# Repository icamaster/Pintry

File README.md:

## Introduction
The Pintry X2 is a two bay NAS (Network Attached Storage) based on the Raspberry Pi Compute Module 4. It uses the ASMedia AS1061 PCIe to Sata bridge to connect up to 2 drives (3.5'/2.5' HDD or 2.5' SSD) to the SoM running a Linux based OS (Raspberry Pi OS).

## Website
Here is a link for additional information: https://www.cezarchirila.com/projects/pintry-x2.html

## Features
* Supports both CM4 and CM4 lite variants
* 2 x SATA ports with power using ASM1061. It should work with both 2.5' and 3.5' HDDs/SSDs but so far it has only been tested with 2.5' SSDs (Western Digital WDS500G2B0A)
* On/Off switch - Can both wake up the CM4 or shut it down (see Device Tree Overlay section) 
* 2 x Fan headers (PWM pin connected, Tach pin unconnected)
* 12V Input Power (max 5A, required for 3.5' drives). 
* USB 2.0 Host port for connecting USB devices and a microUSB Device port for updating the eMMC on CM4. 
* Expander header for access to various GPIO

## Names have a meaning
Pi + Pantry = Pintry

## Device Tree Overlay
Add these changes at the end of the /boot/config.txt to enable specific functionality:
```
# Enable FAN control for FAN0
dtoverlay=gpio-fan,gpiopin=12

# Enable FAN control for FAN1
#dtoverlay=gpio-fan,gpiopin=13

# Enable full functionality of On/Off button
dtoverlay=gpio-shutdown,gpio_pin=21,active_low=0,gpio_pull=off

# Enable UART - UNTESTED
#dtoverlay=uart0,txd0_pin=14,rxd0_pin=15,pin_func=4
#enable_uart=1  
```
Remember to remove the '#' in from of options you want to enable. 

## Kernel
Previously, to be able to use SATA drives with a CM4 you had to recompile the kernel with added SATA support. See instructions [here](https://github.com/geerlingguy/raspberry-pi-pcie-devices/issues/1#issuecomment-717578358) (credit to [Jeff Geerling](github.com/geerlingguy) for instructions). However, newer kernel versions have SATA support built-in, so you should not have to worry about this.

## Enclosure
The enclosure supports 2.5' drives only. It does not have any mounting features for fans, but there is room for a 60mm fan on the bottom as shown in the images below. It does not need supports for printing. Designed in Fusion 360.

For assembly, you will need the following:
* 4 x M3 brass inserts (D0.46mm, L0.57mm)
* 4 x M3x18mm socket screws - for mounting the drives 
* 4 x M3x25mm socket screws - for mounting the drives
* 4 x M3x35mm socket screws - for joining the two halves of the enclosure

## Thermal management
To keep temperatures under control, I have used a RAM heatsink on the ASM1061 IC and a 60mm fan on the bottom of the enclosure tied to the FAN header and controlled via the 'gpio-fan' overlay. It is mounted in such way that it blows air over both the CM4 and the ASM1061.  

## Release
The current latest release is V1.1. This version has not been tested or manufactured yet, therefore I would suggest double checking it if you plan on bulding it!
All the necessary manufacturing and assembly files are in the 'OutputJob/Version' and 'Enclosure' folders.

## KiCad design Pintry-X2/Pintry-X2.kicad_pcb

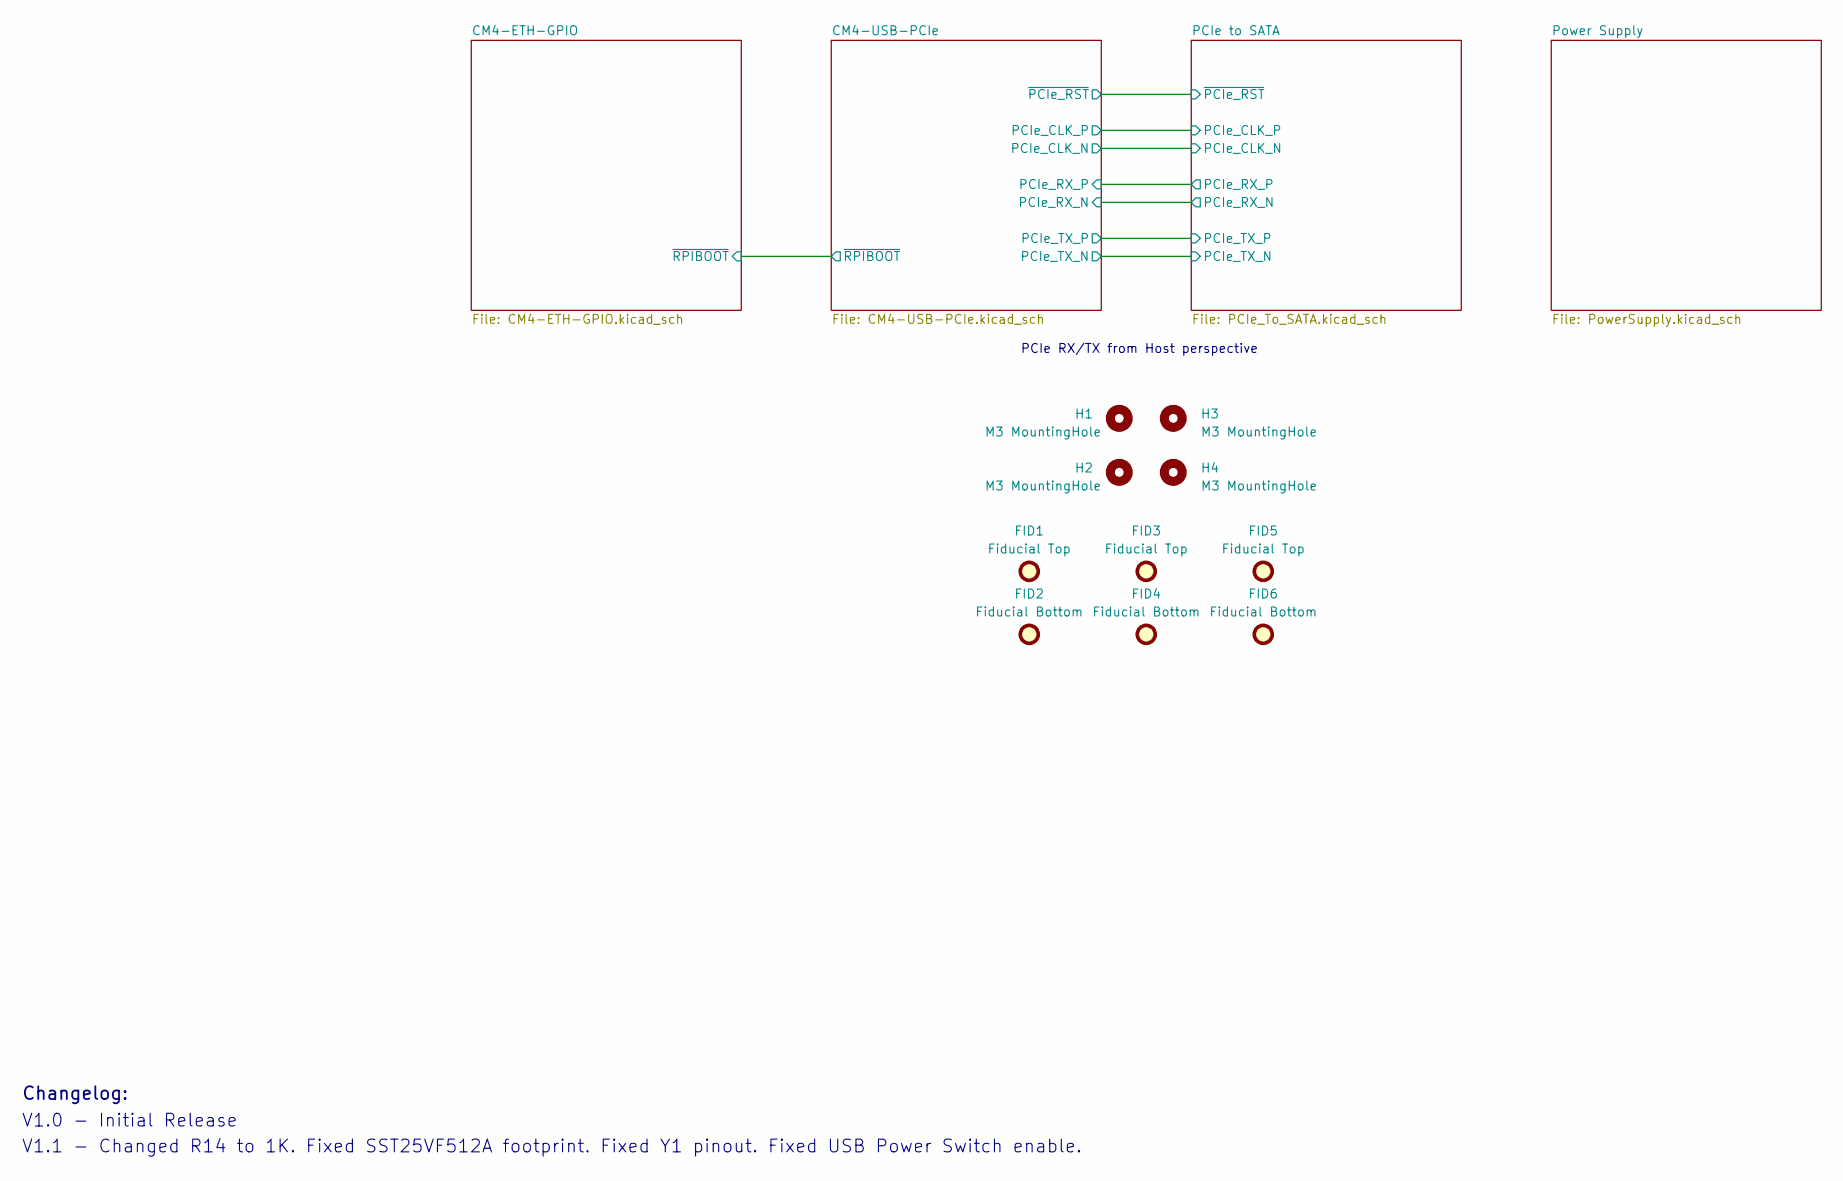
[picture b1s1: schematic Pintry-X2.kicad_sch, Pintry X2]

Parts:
FID1, FID3, FID5: Fiducial Top; Fiducial_1mm_Mask2mm
FID2, FID4, FID6: Fiducial Bottom; Fiducial_1mm_Mask2mm
H1, H2, H3, H4: M3 MountingHole; MountingHole_3.2mm_M3

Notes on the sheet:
V1.0 - Initial Release
Changelog:
PCIe RX/TX from Host perspective
V1.1 - Changed R14 to 1K. Fixed SST25VF512A footprint. Fixed Y1 pinout. Fixed USB Power Switch enable.

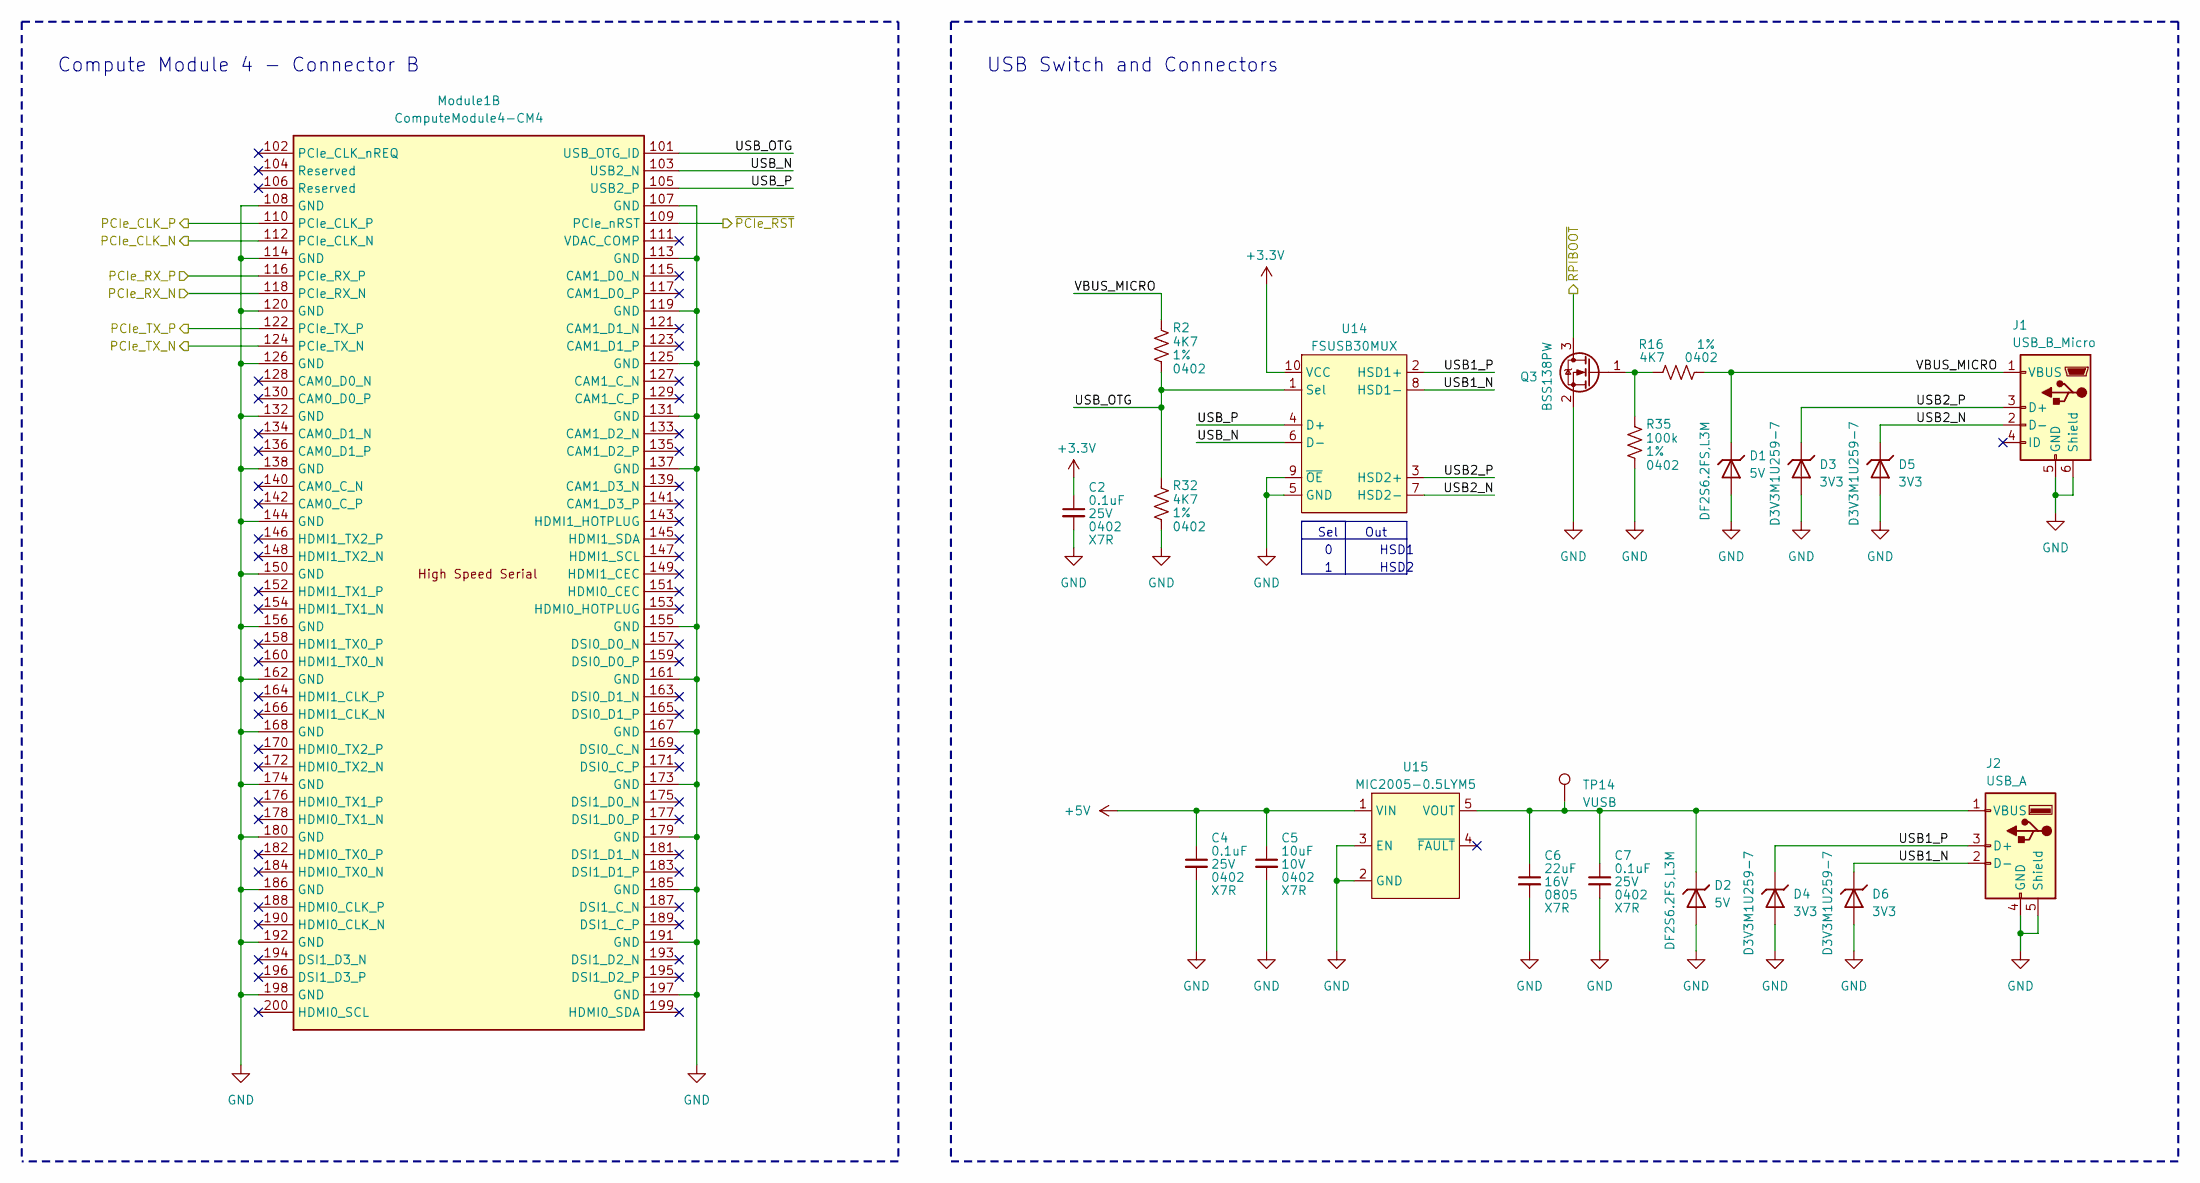
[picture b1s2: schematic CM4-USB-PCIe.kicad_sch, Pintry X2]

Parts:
C2, C4, C7: 0.1uF; C_0402_1005Metric; Voltage Rating 25V
C5: 10uF; C_0402_1005Metric; Voltage Rating 10V
C6: 22uF; C_0805_2012Metric; Voltage Rating 16V; Part Number GRM21BR61A226ME51L
D1, D2: DF2S6.2FS,L3M; D_SOD-923; Part Number DF2S6.2FS,L3M
D3, D4, D5, D6: D3V3M1U259-7; D_SOD-923; Part Number D3V3M1U2S9-7
J1: USB_B_Micro; USB_Micro-B_Amphenol_10103594-0001LF_Horizontal; Part Number 10103594-0001LF
J2: USB_A; USB_A_Amphenol_ICC_73725-11A0BLF_Horizontal; Part Number 73725-11A0BLF
Module1: ComputeModule4-CM4; Raspberry-Pi-4-Compute-Module; Part Number 2x DF40C-100DS-0.4V
Q3: BSS138PW; SOT-323_SC-70; Part Number BSS138PW,115
R2, R16, R32: 4K7; R_0402_1005Metric; Tolerance 1%
R35: 100k; R_0402_1005Metric; Tolerance 1%
TP14: VUSB; TestPoint_Pad_D1.0mm
U14: FSUSB30MUX; MSOP-10_3x3mm_P0.5mm; Part Number FSUSB30MUX
U15: MIC2005-0.5LYM5; SOT-23-5; Part Number MIC2005-0.5LYM5

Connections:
+3V3: C2.1, U14.10 (VCC); also elsewhere on the board
+5V: C4.1, C5.1, U15.1 (VIN); also elsewhere on the board
/CM4-ETH-GPIO/~RPIBOOT: Q3.3 (D); also elsewhere on the board
/CM4-USB-PCIe/PCIe_CLK_N: Module1.112 (PCIe_CLK_N); also elsewhere on the board
/CM4-USB-PCIe/PCIe_CLK_P: Module1.110 (PCIe_CLK_P); also elsewhere on the board
/CM4-USB-PCIe/PCIe_RX_N: Module1.118 (PCIe_RX_N); also elsewhere on the board
/CM4-USB-PCIe/PCIe_RX_P: Module1.116 (PCIe_RX_P); also elsewhere on the board
/CM4-USB-PCIe/PCIe_TX_N: Module1.124 (PCIe_TX_N); also elsewhere on the board
/CM4-USB-PCIe/PCIe_TX_P: Module1.122 (PCIe_TX_P); also elsewhere on the board
/CM4-USB-PCIe/USB1_N: D6.1 (K), J2.2 (D-), U14.8 (HSD1-)
/CM4-USB-PCIe/USB1_P: D4.1 (K), J2.3 (D+), U14.2 (HSD1+)
/CM4-USB-PCIe/USB2_N: D5.1 (K), J1.2 (D-), U14.7 (HSD2-)
/CM4-USB-PCIe/USB2_P: D3.1 (K), J1.3 (D+), U14.3 (HSD2+)
/CM4-USB-PCIe/USB_N: Module1.103 (USB2_N), U14.6 (D-)
/CM4-USB-PCIe/USB_OTG: Module1.101 (USB_OTG_ID), R2.2, R32.1, U14.1 (Sel)
/CM4-USB-PCIe/USB_P: Module1.105 (USB2_P), U14.4 (D+)
/CM4-USB-PCIe/VBUS_MICRO: D1.1 (K), J1.1 (VBUS), R2.1, R16.2
/CM4-USB-PCIe/~PCIe_RST: Module1.109 (PCIe_nRST); also elsewhere on the board
GND: C2.2, C4.2, C5.2, C6.2, C7.2, D1.2 (A), D2.2 (A), D3.2 (A), D4.2 (A), D5.2 (A), D6.2 (A), J1.5 (GND), J1.6 (Shield), J2.4 (GND), J2.5 (Shield), Module1.107 (GND), Module1.108 (GND), Module1.113 (GND), Module1.114 (GND), Module1.119 (GND), Module1.120 (GND), Module1.125 (GND), Module1.126 (GND), Module1.131 (GND), Module1.132 (GND), Module1.137 (GND), Module1.138 (GND), Module1.144 (GND), Module1.150 (GND), Module1.155 (GND), Module1.156 (GND), Module1.161 (GND), Module1.162 (GND), Module1.167 (GND), Module1.168 (GND), Module1.173 (GND), Module1.174 (GND), Module1.179 (GND), Module1.180 (GND), Module1.185 (GND), Module1.186 (GND), Module1.191 (GND), Module1.192 (GND), Module1.197 (GND), Module1.198 (GND), Q3.2 (S), R32.2, R35.2, U14.5 (GND), U14.9 (~OE), U15.2 (GND), U15.3 (EN); also elsewhere on the board
unnamed: C6.1, C7.1, D2.1 (K), J2.1 (VBUS), TP14.1, U15.5 (VOUT)
unnamed: Q3.1 (G), R16.1, R35.1

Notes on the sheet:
Compute Module 4 - Connector B
Sel Out
USB Switch and Connectors
1 HSD2
0 HSD1

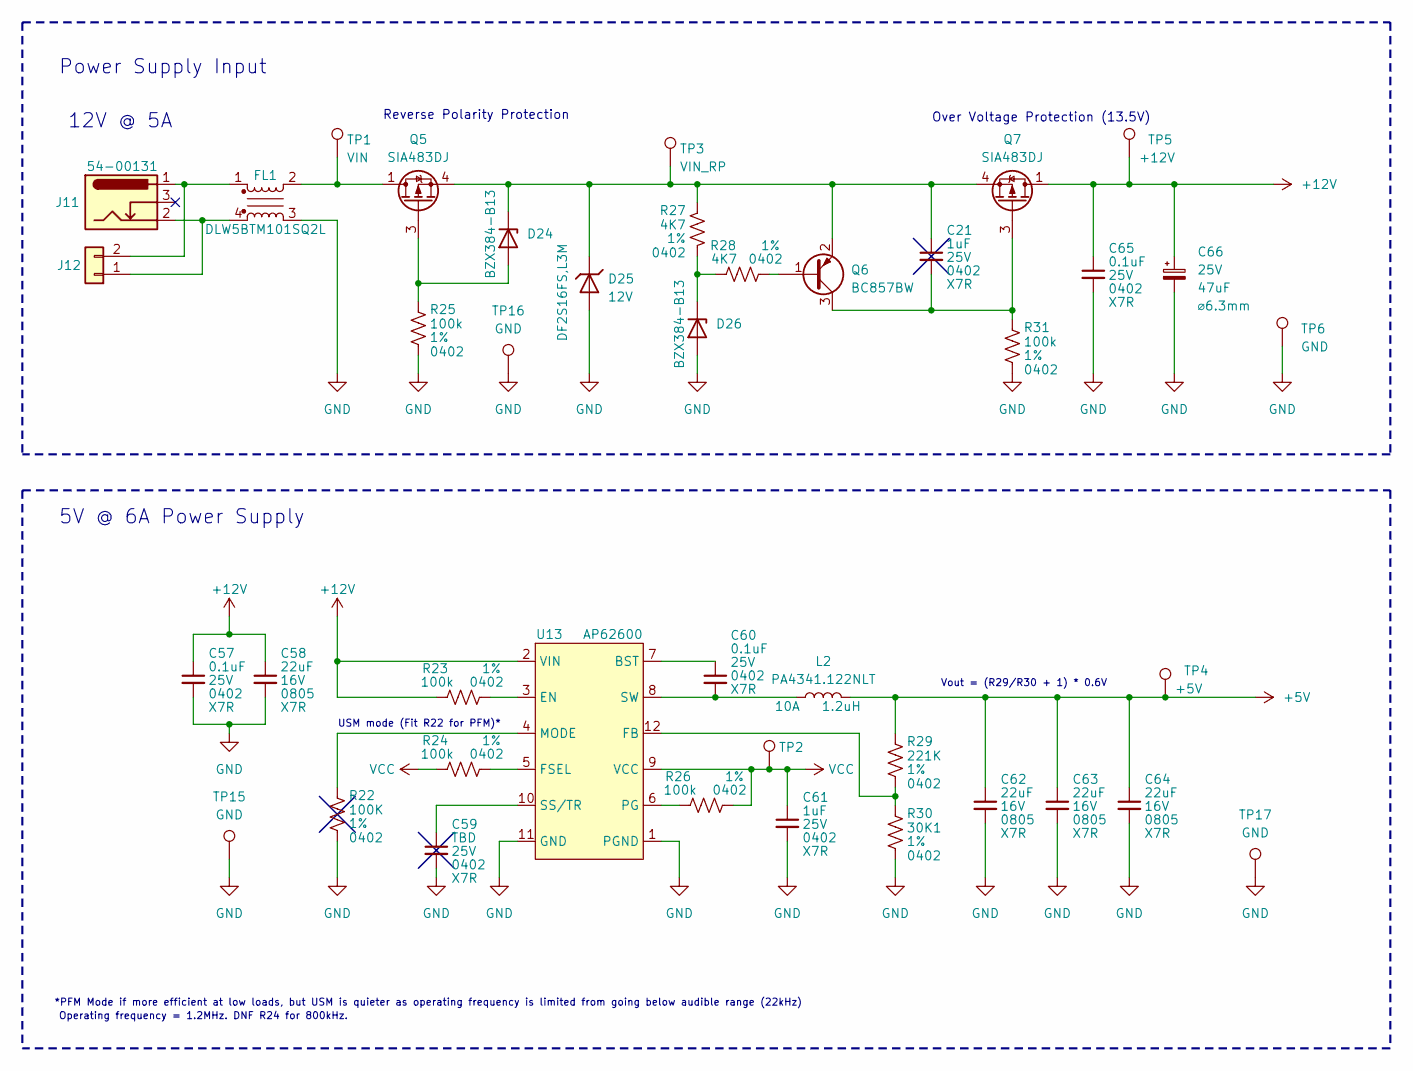
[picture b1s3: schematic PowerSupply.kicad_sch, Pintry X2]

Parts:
C21, C61: 1uF; C_0402_1005Metric; Voltage Rating 25V
C57, C60, C65: 0.1uF; C_0402_1005Metric; Voltage Rating 25V
C58: 22uF; C_0805_2012Metric; Voltage Rating 16V; Part Number CL21A226MOQNNNE
C59: TBD; C_0402_1005Metric; Voltage Rating 25V
C62, C63, C64: 22uF; C_0805_2012Metric; Voltage Rating 16V; Part Number GRM21BR61A226ME51L
C66: 865080443007; CP_Elec_6.3x5.4; Voltage 25V; Part Number 865080443007
D24, D26: BZX384-B13; D_SOD-323; Part Number BZX384-B13,115
D25: DF2S16FS,L3M; D_SOD-923; Part Number DF2S16FS,L3M
FL1: DLW5BTM101SQ2L; Part Number DLW5BTM101SQ2L
J11: 54-00131; Part Number 54-00131
J12: Alternate Power Connector; SolderWire-1sqmm_1x02_P5.4mm_D1.4mm_OD2.7mm
L2: PA4341.122NLT; Pulse_PA4341; Current Rating 10A; Part Number PA4341.122NLT
Q5, Q7: SIA483DJ; Vishay_PowerPAK_SC70-6L_Single; PartNumber SIA483DJ-T1-GE3
Q6: BC857BW; SOT-323_SC-70; Part Number BC857BW,135
R22: 100K; R_0402_1005Metric; Tolerance 1%
R23, R24, R25, R26, R31: 100k; R_0402_1005Metric; Tolerance 1%
R27, R28: 4K7; R_0402_1005Metric; Tolerance 1%
R29: 221K; R_0402_1005Metric; Tolerance 1%
R30: 30K1; R_0402_1005Metric; Tolerance 1%
TP1: VIN; TestPoint_Pad_D1.0mm
TP2: VCC; TestPoint_Pad_D1.0mm
TP3: VIN_RP; TestPoint_Pad_D1.0mm
TP4: +5V; TestPoint_Pad_D1.0mm
TP5: +12V; TestPoint_Pad_D1.0mm
TP6, TP15, TP16, TP17: GND; TestPoint_Pad_D1.0mm
U13: AP62600; V-QFN2030-12 (Type A); Part Number AP62600SJ-7

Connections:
+5V: C62.1, C63.1, C64.1, L2.2, R29.1, TP4.1; also elsewhere on the board
+12V: C57.1, C58.1, C65.1, C66.1, Q7.1 (D), R23.1, TP5.1, U13.2 (VIN); also elsewhere on the board
GND: C57.2, C58.2, C59.2, C61.2, C62.2, C63.2, C64.2, C65.2, C66.2, D25.2 (A), D26.2 (A), FL1.3, R22.2, R25.2, R30.2, R31.2, TP6.1, TP15.1, TP16.1, TP17.1, U13.1 (PGND), U13.11 (GND); also elsewhere on the board
unnamed: C21.1, D24.1 (K), D25.1 (K), Q5.4 (S), Q6.2 (E), Q7.4 (S), R27.1, TP3.1
unnamed: C21.2, Q6.3 (C), Q7.3 (G), R31.1
unnamed: C59.1, U13.10 (SS/TR)
unnamed: C60.1, U13.7 (BST)
unnamed: C60.2, L2.1, U13.8 (SW)
unnamed: D24.2 (A), Q5.3 (G), R25.1
unnamed: D26.1 (K), R27.2, R28.1
unnamed: FL1.1, J11.1 (A), J12.2
unnamed: FL1.2, Q5.1 (D), TP1.1
unnamed: FL1.4, J11.2 (B), J12.1
unnamed: Q6.1 (B), R28.2
unnamed: R22.1, U13.4 (MODE)
unnamed: R23.2, U13.3 (EN)
unnamed: R24.2, U13.5 (FSEL)
unnamed: R26.1, U13.6 (PG)
unnamed: R29.2, R30.1, U13.12 (FB)
VCC: C61.1, R24.1, R26.2, TP2.1, U13.9 (VCC)

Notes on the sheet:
5V @ 6A Power Supply
Power Supply Input
12V @ 5A
USM mode (Fit R22 for PFM)*
Vout = (R29/R30 + 1) * 0.6V
Operating frequency = 1.2MHz. DNF R24 for 800kHz.
*PFM Mode if more efficient at low loads, but USM is quieter as operating frequency is limited from going below audible range (22kHz)
Reverse Polarity Protection
Over Voltage Protection (13.5V)

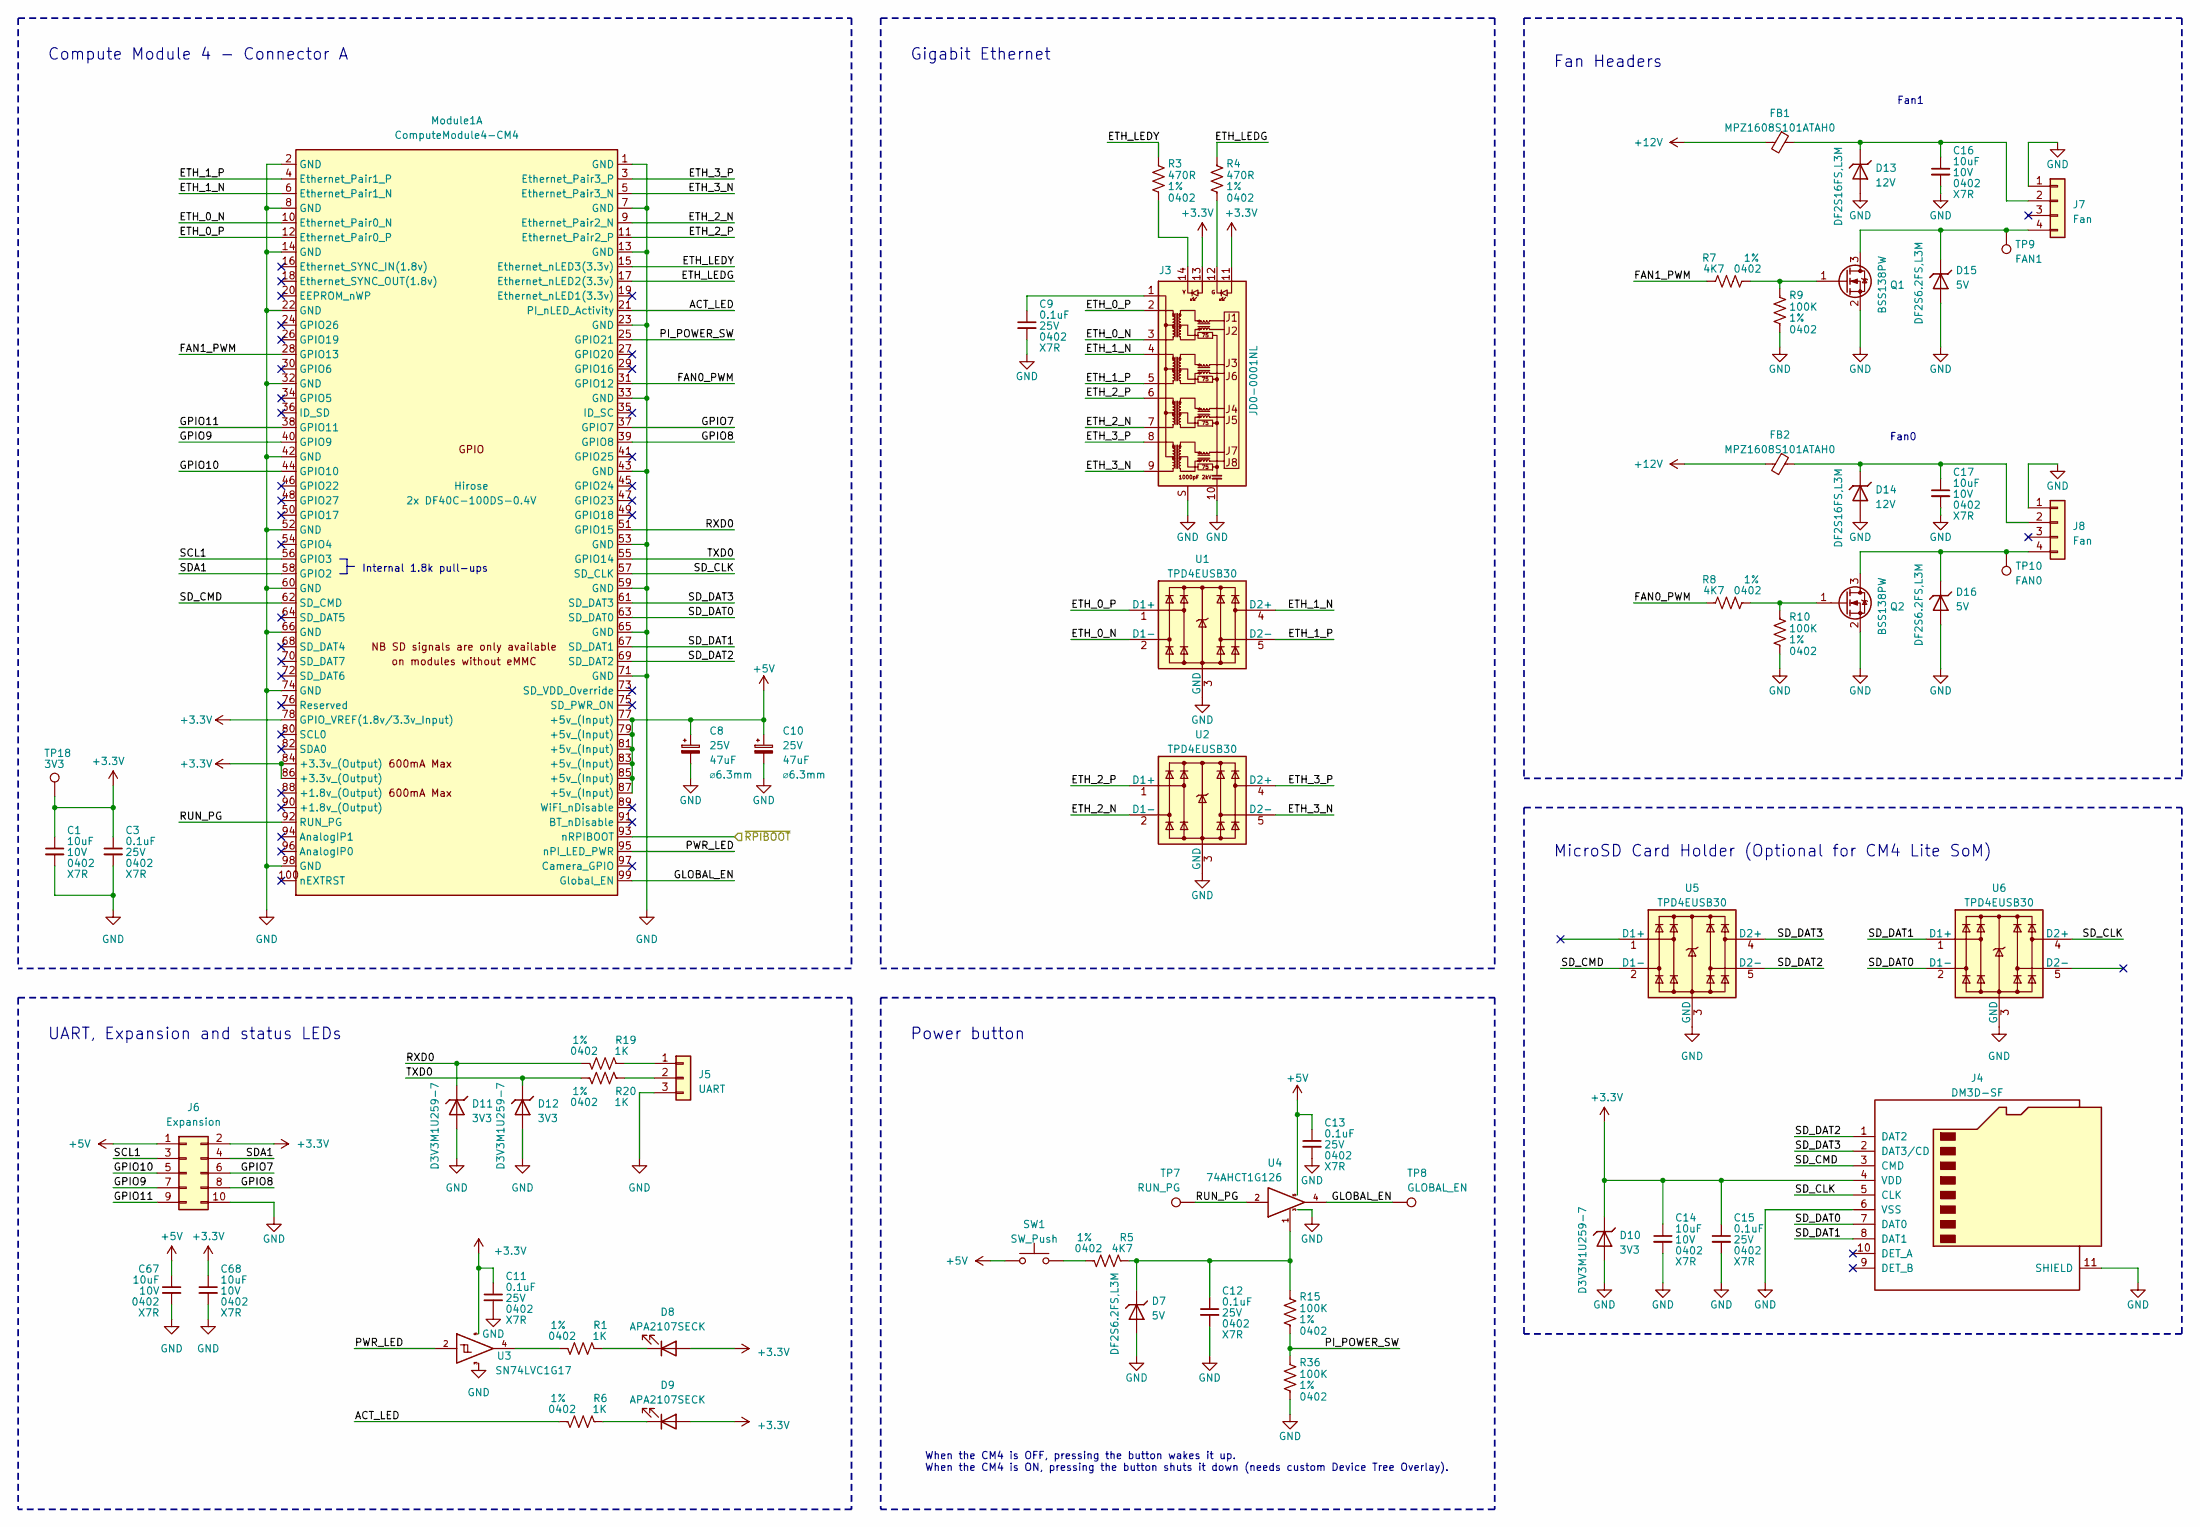
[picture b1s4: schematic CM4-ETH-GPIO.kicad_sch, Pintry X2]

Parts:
C1, C14, C16, C17, C67, C68: 10uF; C_0402_1005Metric; Voltage Rating 10V
C3, C9, C11, C12, C13, C15: 0.1uF; C_0402_1005Metric; Voltage Rating 25V
C8, C10: 865080443007; CP_Elec_6.3x5.4; Voltage 25V; Part Number 865080443007
D7, D15, D16: DF2S6.2FS,L3M; D_SOD-923; Part Number DF2S6.2FS,L3M
D8, D9: APA2107SECK; PartNumber APA2107SECK/J4-PRV
D10, D11, D12: D3V3M1U259-7; D_SOD-923; Part Number D3V3M1U2S9-7
D13, D14: DF2S16FS,L3M; D_SOD-923; Part Number DF2S16FS,L3M
FB1, FB2: MPZ1608S101ATAH0; L_0603_1608Metric; Part Number MPZ1608S101ATAH0
J3: JD0-0001NL; Pulse-JD0-0001NL-0-0-MFG; Part Number JD0-0001NL
J4: DM3D-SF; microSD_HC_Hirose_DM3D-SF; Part Number DM3D-SF
J5: UART; PinHeader_1x03_P2.54mm_Vertical; Part Number PH1-03-UA
J6: Expansion; PinHeader_2x05_P2.54mm_Vertical; Part Number 2PH2-10-UA
J7, J8: Fan; Molex_KK-254_AE-6410-04A_1x04_P2.54mm_Vertical; Part Number 47053-1000
Module1: ComputeModule4-CM4; Raspberry-Pi-4-Compute-Module; Part Number 2x DF40C-100DS-0.4V
Q1, Q2: BSS138PW; SOT-323_SC-70; Part Number BSS138PW,115
R1, R6, R19, R20: 1K; R_0402_1005Metric; Tolerance 1%
R3, R4: 470R; R_0402_1005Metric; Tolerance 1%
R5, R7, R8: 4K7; R_0402_1005Metric; Tolerance 1%
R9, R10, R15, R36: 100K; R_0402_1005Metric; Tolerance 1%
SW1: SW_Push; SW_Tactile_SPST_Angled_PTS645Vx58-2LFS; Part Number 1-1825027-4
TP7: RUN_PG; TestPoint_Pad_D1.0mm
TP8: GLOBAL_EN; TestPoint_Pad_D1.0mm
TP9: FAN1; TestPoint_Pad_D1.0mm
TP10: FAN0; TestPoint_Pad_D1.0mm
TP18: 3V3; TestPoint_Pad_D1.0mm
U1, U2, U5, U6: TPD4EUSB30; USON-10_2.5x1.0mm_P0.5mm; Part Number TPD4EUSB30DQAR
U3: SN74LVC1G17; SOT-23-5; Part Number SN74LVC1G17DBVR
U4: 74AHCT1G126; SOT-353_SC-70-5; Part Number 74AHCT1G126SE-7

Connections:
+3V3: C1.1, C3.1, C11.1, C14.1, C15.1, C68.1, D8.2 (A), D9.2 (A), D10.1 (K), J3.11, J3.13, J4.4 (VDD), J6.2, Module1.78 (GPIO_VREF(1.8v/3.3v_Input)), Module1.84 (+3.3v_(Output)), Module1.86 (+3.3v_(Output)), TP18.1, U3.5 (VCC); also elsewhere on the board
+5V: C8.1, C10.1, C13.1, C67.1, J6.1, Module1.77 (+5v_(Input)), Module1.79 (+5v_(Input)), Module1.81 (+5v_(Input)), Module1.83 (+5v_(Input)), Module1.85 (+5v_(Input)), Module1.87 (+5v_(Input)), SW1.1, U4.5 (VCC); also elsewhere on the board
+12V: FB1.2, FB2.2; also elsewhere on the board
/CM4-ETH-GPIO/ACT_LED: Module1.21 (PI_nLED_Activity), R6.2
/CM4-ETH-GPIO/ETH_0_N: J3.3, Module1.10 (Ethernet_Pair0_N), U1.2 (D1-), U1.9
/CM4-ETH-GPIO/ETH_0_P: J3.2, Module1.12 (Ethernet_Pair0_P), U1.1 (D1+), U1.10
/CM4-ETH-GPIO/ETH_1_N: J3.4, Module1.6 (Ethernet_Pair1_N), U1.4 (D2+), U1.7
/CM4-ETH-GPIO/ETH_1_P: J3.5, Module1.4 (Ethernet_Pair1_P), U1.5 (D2-), U1.6
/CM4-ETH-GPIO/ETH_2_N: J3.7, Module1.9 (Ethernet_Pair2_N), U2.2 (D1-), U2.9
/CM4-ETH-GPIO/ETH_2_P: J3.6, Module1.11 (Ethernet_Pair2_P), U2.1 (D1+), U2.10
/CM4-ETH-GPIO/ETH_3_N: J3.9, Module1.5 (Ethernet_Pair3_N), U2.5 (D2-), U2.6
/CM4-ETH-GPIO/ETH_3_P: J3.8, Module1.3 (Ethernet_Pair3_P), U2.4 (D2+), U2.7
/CM4-ETH-GPIO/ETH_LEDG: Module1.17 (Ethernet_nLED2(3.3v)), R4.1
/CM4-ETH-GPIO/ETH_LEDY: Module1.15 (Ethernet_nLED3(3.3v)), R3.1
/CM4-ETH-GPIO/FAN0_PWM: Module1.31 (GPIO12), R8.1
/CM4-ETH-GPIO/FAN1_PWM: Module1.28 (GPIO13), R7.1
/CM4-ETH-GPIO/GLOBAL_EN: Module1.99 (Global_EN), TP8.1, U4.4
/CM4-ETH-GPIO/GPIO7: J6.6, Module1.37 (GPIO7)
/CM4-ETH-GPIO/GPIO8: J6.8, Module1.39 (GPIO8)
/CM4-ETH-GPIO/GPIO9: J6.7, Module1.40 (GPIO9)
/CM4-ETH-GPIO/GPIO10: J6.5, Module1.44 (GPIO10)
/CM4-ETH-GPIO/GPIO11: J6.9, Module1.38 (GPIO11)
/CM4-ETH-GPIO/PI_POWER_SW: Module1.25 (GPIO21), R15.2, R36.1
/CM4-ETH-GPIO/PWR_LED: Module1.95 (nPI_LED_PWR), U3.2
/CM4-ETH-GPIO/RUN_PG: Module1.92 (RUN_PG), TP7.1, U4.2
/CM4-ETH-GPIO/RXD0: D11.1 (K), Module1.51 (GPIO15), R19.2
/CM4-ETH-GPIO/SCL1: J6.3, Module1.56 (GPIO3)
/CM4-ETH-GPIO/SDA1: J6.4, Module1.58 (GPIO2)
/CM4-ETH-GPIO/SD_CLK: J4.5 (CLK), Module1.57 (SD_CLK), U6.4 (D2+), U6.7
/CM4-ETH-GPIO/SD_CMD: J4.3 (CMD), Module1.62 (SD_CMD), U5.2 (D1-), U5.9
/CM4-ETH-GPIO/SD_DAT0: J4.7 (DAT0), Module1.63 (SD_DAT0), U6.2 (D1-), U6.9
/CM4-ETH-GPIO/SD_DAT1: J4.8 (DAT1), Module1.67 (SD_DAT1), U6.1 (D1+), U6.10
/CM4-ETH-GPIO/SD_DAT2: J4.1 (DAT2), Module1.69 (SD_DAT2), U5.5 (D2-), U5.6
/CM4-ETH-GPIO/SD_DAT3: J4.2 (DAT3/CD), Module1.61 (SD_DAT3), U5.4 (D2+), U5.7
/CM4-ETH-GPIO/TXD0: D12.1 (K), Module1.55 (GPIO14), R20.2
/CM4-ETH-GPIO/~RPIBOOT: Module1.93 (nRPIBOOT); also elsewhere on the board
GND: C1.2, C3.2, C8.2, C9.2, C10.2, C11.2, C12.2, C13.2, C14.2, C15.2, C16.2, C17.2, C67.2, C68.2, D7.2 (A), D10.2 (A), D11.2 (A), D12.2 (A), D13.2 (A), D14.2 (A), D15.2 (A), D16.2 (A), J3.10, J3.S, J4.6 (VSS), J4.11 (SHIELD), J5.3, J6.10, J7.1, J8.1, Module1.1 (GND), Module1.2 (GND), Module1.7 (GND), Module1.8 (GND), Module1.13 (GND), Module1.14 (GND), Module1.22 (GND), Module1.23 (GND), Module1.32 (GND), Module1.33 (GND), Module1.42 (GND), Module1.43 (GND), Module1.52 (GND), Module1.53 (GND), Module1.59 (GND), Module1.60 (GND), Module1.65 (GND), Module1.66 (GND), Module1.71 (GND), Module1.74 (GND), Module1.98 (GND), Q1.2 (S), Q2.2 (S), R9.2, R10.2, R36.2, U1.3 (GND), U1.8 (GND), U2.3 (GND), U2.8 (GND), U3.3 (GND), U4.3 (GND), U5.3 (GND), U5.8 (GND), U6.3 (GND), U6.8 (GND); also elsewhere on the board
unnamed: C9.1, J3.1
unnamed: C12.1, D7.1 (K), R5.1, R15.1, U4.1
unnamed: C16.1, D13.1 (K), FB1.1, J7.2
unnamed: C17.1, D14.1 (K), FB2.1, J8.2
unnamed: D8.1 (K), R1.1
unnamed: D9.1 (K), R6.1
unnamed: D15.1 (K), J7.4, Q1.3 (D), TP9.1
unnamed: D16.1 (K), J8.4, Q2.3 (D), TP10.1
unnamed: J3.12, R4.2
unnamed: J3.14, R3.2
unnamed: J5.1, R19.1
unnamed: J5.2, R20.1
unnamed: Q1.1 (G), R7.2, R9.1
unnamed: Q2.1 (G), R8.2, R10.1
unnamed: R1.2, U3.4
unnamed: R5.2, SW1.2

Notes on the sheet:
Gigabit Ethernet
Internal 1.8k pull-ups
When the CM4 is OFF, pressing the button wakes it up. When the CM4 is ON, pressing the button shuts it down (needs custom Device Tree Overlay).
UART, Expansion and status LEDs
MicroSD Card Holder (Optional for CM4 Lite SoM)
Fan1
Fan0
Fan Headers
Power button
Compute Module 4 - Connector A
